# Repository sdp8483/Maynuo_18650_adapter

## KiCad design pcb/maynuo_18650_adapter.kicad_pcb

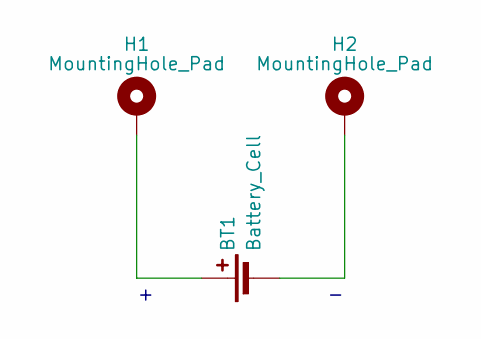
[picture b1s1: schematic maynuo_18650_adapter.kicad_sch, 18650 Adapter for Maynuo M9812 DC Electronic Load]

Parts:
BT1: Battery_Cell; 18650_battery_holder_PCB_Pins
H1, H2: MountingHole_Pad; MountingHole_6.4mm_M6_DIN965_Pad

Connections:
unnamed: BT1.1 (+), H1.1
unnamed: BT1.2 (-), H2.1

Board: 2 copper layers, 3 parts (0 on the bottom side), 2 nets, no tracks yet.

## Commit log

2024-06-11 init commit
2024-06-11 del lock
